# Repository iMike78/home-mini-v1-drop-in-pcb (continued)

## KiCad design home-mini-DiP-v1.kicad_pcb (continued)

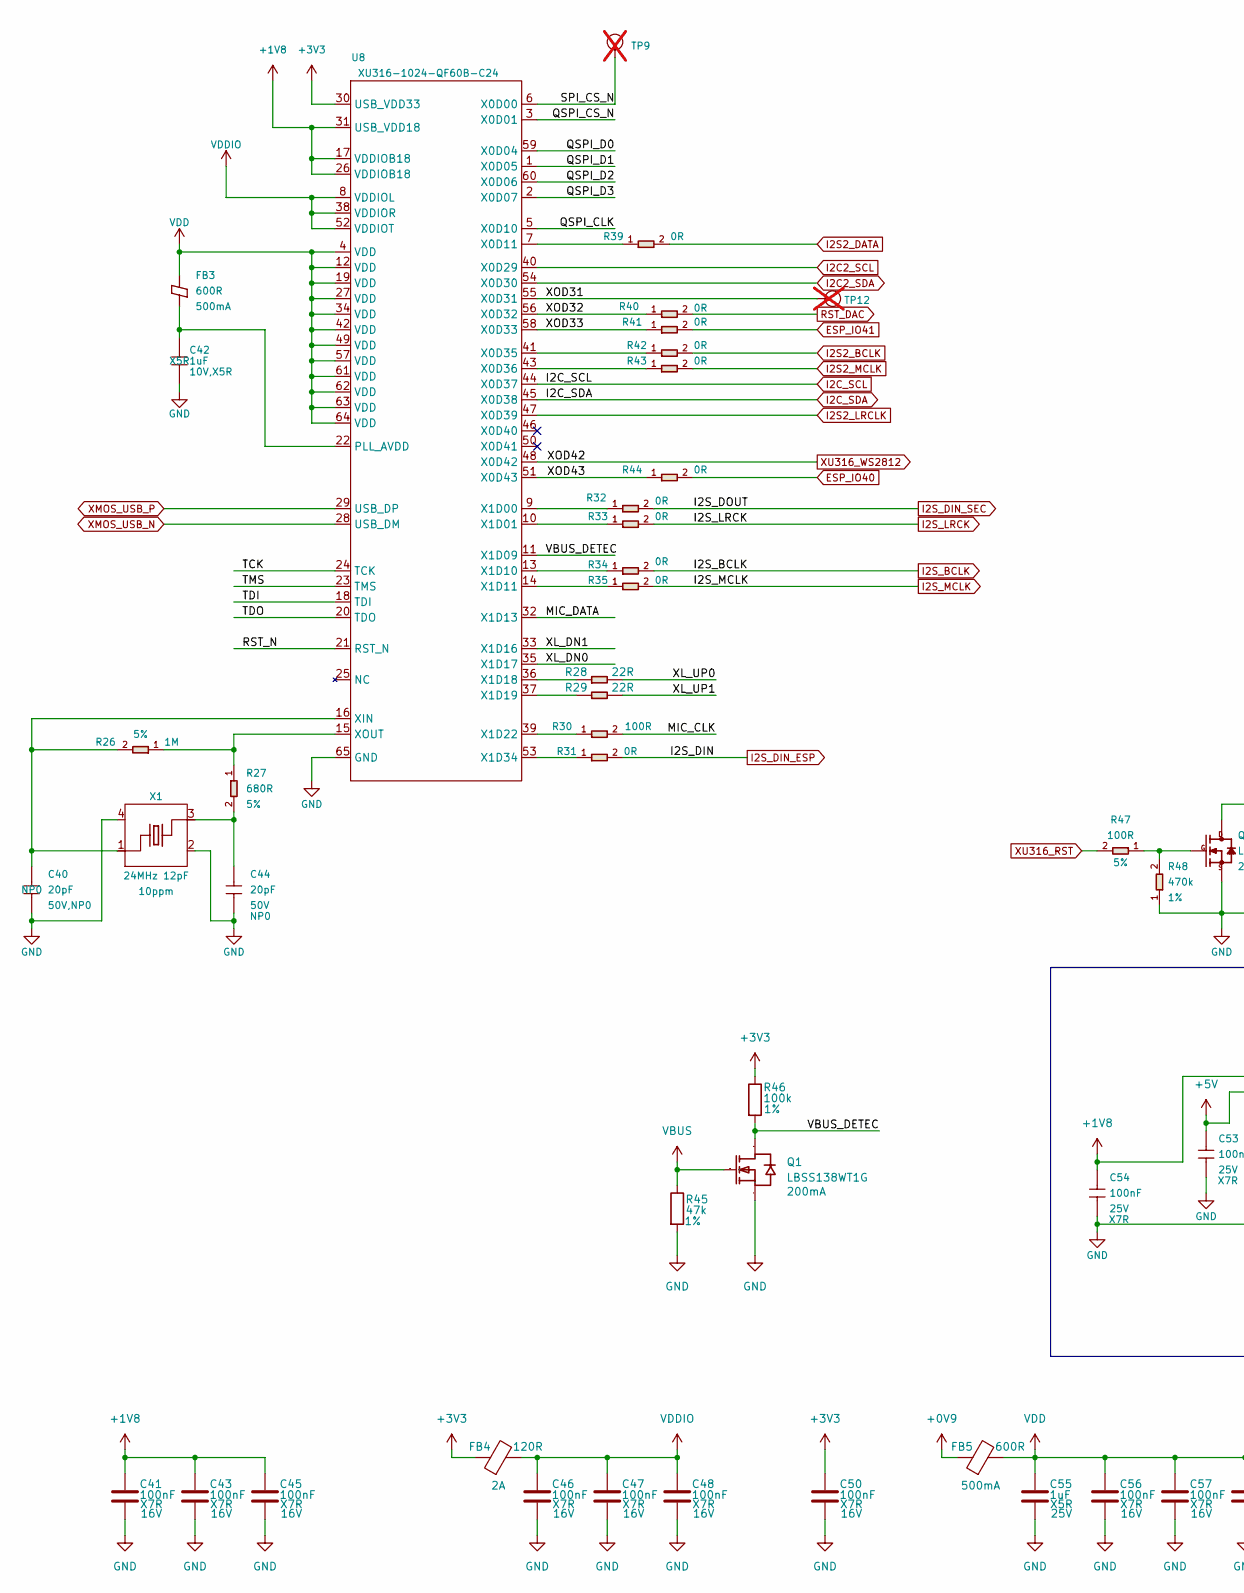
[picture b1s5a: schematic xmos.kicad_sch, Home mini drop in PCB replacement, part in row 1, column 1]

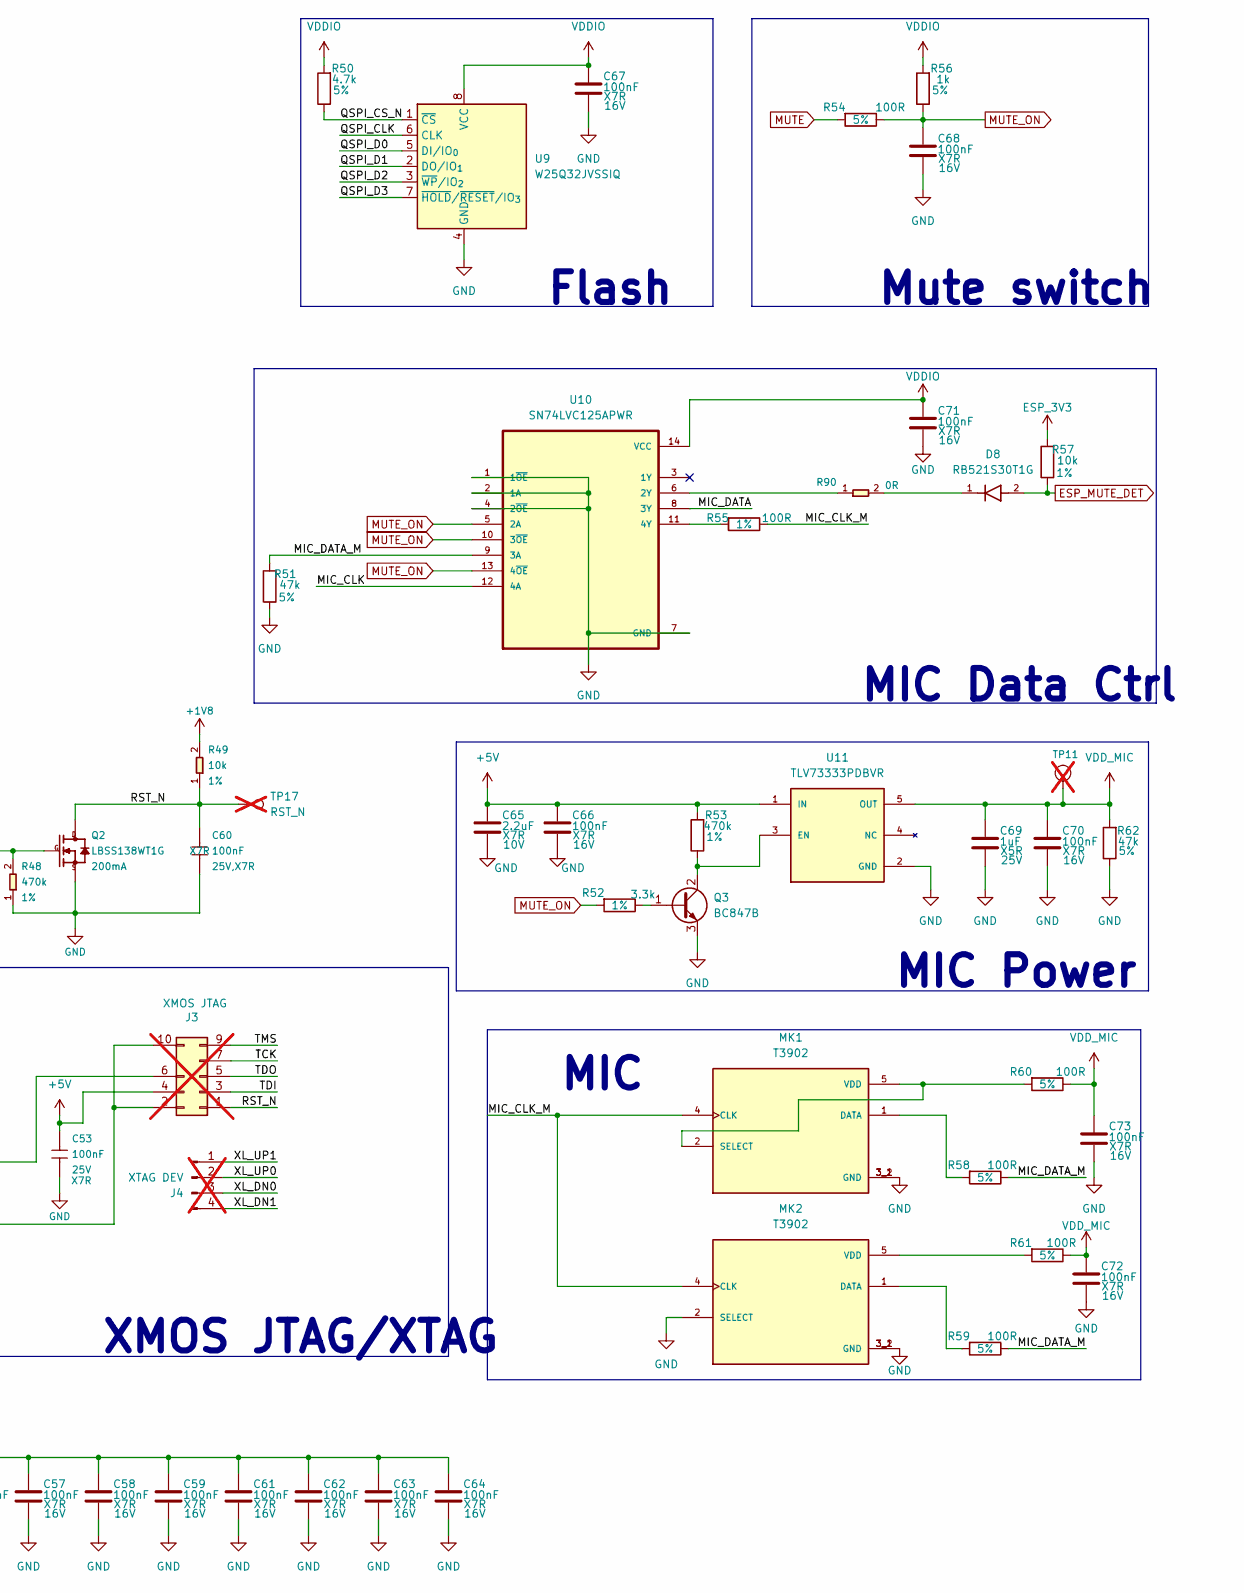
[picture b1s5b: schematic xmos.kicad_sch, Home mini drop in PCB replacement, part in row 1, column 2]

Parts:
C40: 20pF; C_0402_1005Metric; Voltage Rating 50V,NP0; Voltage 50V; MPN 0402CG200J500NT; LCSC Part # C1554
C41, C43, C45, C46, C47, C48, C50, C56, C57, C58, C59, C61, C62, C63, C64, C66, C67, C68, C70, C71, C72, C73: 100nF; C_0402_1005Metric; Voltage 16V; Manufacturer Part CL05B104KO5NNNC; LCSC Part # C1525
C42: 1uF; C_0402_1005Metric; Voltage Rating 10V,X5R; Voltage 25V; MPN CL05A105KA5NQNC; LCSC Part # C52923
C44: 20pF; C_0402_1005Metric; Voltage Rating 50V; Voltage 50V; MPN 0402CG200J500NT; LCSC Part # C1554
C53, C54: 100nF; C_0402_1005Metric; Voltage Rating 25V; Voltage 16V; MPN CL05B104KO5NNNC; LCSC Part # C1525
C55, C69: 1uF; C_0402_1005Metric; Voltage 25V; Manufacturer Part CL05A105KA5NQNC; LCSC Part # C52923
C60: 100nF; C_0402_1005Metric; Voltage Rating 25V,X7R; MPN CL05B104KO5NNNC; LCSC Part # C1525
C65: 2.2uF; C_0603_1608Metric; Voltage 10V; Manufacturer Part GRM188R71A225KE15D; LCSC Part # C86018
D8: RB521S30T1G; DIOM168X70N; Manufacturer Part RB521S30T1G; LCSC Part # C27636108
FB3: 600R; BLM18PG121SN1D; Rating 500mA; MPN BLM18KG601SN1D; LCSC Part # C85833
FB4: 120R; BLM18PG121SN1D; Manufacturer Part BLM18PG121SN1D; LCSC Part # C14709
FB5: 600R; BLM18PG121SN1D; Manufacturer Part BLM18KG601SN1D; LCSC Part # C85833
J3: XMOS JTAG; PinHeader_2x05_P2.54mm_Vertical; not fitted
J4: XTAG DEV; PinHeader_1x04_P2.54mm_Vertical; not fitted
MK1, MK2: T3902; MIC_T3902; Manufacturer Part MMICT390200012; LCSC Part # C3171752
Q1: LBSS138WT1G; SOT-323_SC-70; Manufacturer Part LBSS138WT1G; LCSC Part # C383201
Q2: LBSS138WT1G; SOT-323_SC-70; Rating 200mA; MPN LBSS138WT1G; LCSC Part # C383201
Q3: BC847B; SOT-23; Manufacturer Part BC847B; LCSC Part # C20069135
R26: 1M; R_0402_1005Metric; Power Rating 5%; MPN 0402WGF1004TCE; LCSC Part # C26083
R27: 680R; R_0402_1005Metric; Power Rating 5%; MPN 0402WGF6800TCE; LCSC Part # C25130
R28, R29: 22R; R_0402_1005Metric; Power Rating 5%; MPN 0402WGF220JTCE; LCSC Part # C25092
R30, R47: 100R; R_0402_1005Metric; Power Rating 5%; MPN 0402WGF1000TCE; LCSC Part # C25076
R31, R32, R33, R34, R35, R41, R42, R43, R44: 0R; R_0402_1005Metric; Power Rating 5%; MPN 0402WGF0000TCE; LCSC Part # C17168
R39, R40, R90: 0R; R_0402_1005Metric; Tolerance 5%; MPN 0402WGF0000TCE; LCSC Part # C17168
R45: 47k; R_0402_1005Metric; Tolerance 1%; Manufacturer Part 0402WGF4702TCE; LCSC Part # C25792
R46: 100k; R_0402_1005Metric; Tolerance 1%; Manufacturer Part 0402WGJ0104TCE; LCSC Part # C25530
R48: 470k; R_0402_1005Metric; Power Rating 1%; MPN 0402WGF4703TCE; LCSC Part # C25790
R49: 10k; R_0402_1005Metric; Power Rating 1%; MPN 0402WGF1002TCE; LCSC Part # C25744
R50: 4.7k; R_0402_1005Metric; Tolerance 5%; Manufacturer Part 0402WGF4701TCE; LCSC Part # C25900
R51, R62: 47k; R_0402_1005Metric; Tolerance 5%; Manufacturer Part 0402WGF4702TCE; LCSC Part # C25792
R52: 3.3k; R_0402_1005Metric; Tolerance 1%; Manufacturer Part 0402WGF3301TCE; LCSC Part # C25890
R53: 470k; R_0402_1005Metric; Tolerance 1%; Manufacturer Part 0402WGF4703TCE; LCSC Part # C25790
R54: 100R; R_0402_1005Metric; Tolerance 5%; Power Rating 5%; Manufacturer Part 0402WGF1000TCE; LCSC Part # C25076
R55: 100R; R_0402_1005Metric; Tolerance 1%; Manufacturer Part 0402WGF1000TCE; LCSC Part # C25076
R56: 1k; R_0402_1005Metric; Tolerance 5%; Manufacturer Part 0402WGF1001TCE; LCSC Part # C11702
R57: 10k; R_0402_1005Metric; Tolerance 1%; Manufacturer Part 0402WGF1002TCE; LCSC Part # C25744
R58, R59, R60, R61: 100R; R_0402_1005Metric; Tolerance 5%; Manufacturer Part 0402WGF1000TCE; LCSC Part # C25076
TP9, TP11: TEST-POINT; TestPoint_Pad_D1.0mm; not fitted
TP12: Test Point; TestPoint_Pad_D1.0mm; Part Type Test Point; not fitted
TP17: RST_N; TestPoint_Pad_D1.0mm; not fitted
U8: XU316-1024-QF60B-C24​; XU316-1024-QF60B-C24; MPN XU316-1024-QF60B-C24; LCSC Part # C6617472
U9: W25Q32JVSSIQ; SOIC-8_5.3x5.3mm_P1.27mm; Manufacturer Part W25Q32JVSSIQ; LCSC Part # C179173
U10: SN74LVC125APWR; SOP65P640X120-14N; Manufacturer Part SN74LVC125APWR; LCSC Part # C7813
U11: TLV73333PDBVR; Manufacturer Part TLV73333PDBVR; LCSC Part # C134139
X1: 24MHz 12pF; X4-SMD-2.0X1.6MM; Rating 10ppm; MPN 7F24000E12UCG; LCSC Part # C252273

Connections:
+0V9: FB5.1; also elsewhere on the board
+1V8: C41.1, C43.1, C45.1, C54.1, J3.6, R49.2, U8.17 (VDDIOB18), U8.26 (VDDIOB18), U8.31 (USB_VDD18); also elsewhere on the board
+3V3: C50.1, FB4.1, R46.1, U8.30 (USB_VDD33); also elsewhere on the board
+5V: C53.1, C65.1, C66.1, J3.4, R53.2, U11.1 (IN); also elsewhere on the board
/XMOS/MIC_CLK: R30.2, U10.12 (4A)
/XMOS/MIC_CLK_M: MK1.4 (CLK), MK2.4 (CLK), R55.1
/XMOS/MIC_DATA: U8.32 (X1D13), U10.8 (3Y)
/XMOS/MIC_DATA_M: R51.2, R58.1, R59.1, U10.9 (3A)
/XMOS/QSPI_CLK: U8.5 (X0D10), U9.6 (CLK)
/XMOS/QSPI_CS_N: R50.1, U8.3 (X0D01), U9.1 (~CS)
/XMOS/QSPI_D0: U8.59 (X0D04), U9.5 (DI/IO_{0})
/XMOS/QSPI_D1: U8.1 (X0D05), U9.2 (DO/IO_{1})
/XMOS/QSPI_D2: U8.60 (X0D06), U9.3 (~WP/IO_{2})
/XMOS/QSPI_D3: U8.2 (X0D07), U9.7 (~HOLD/~RESET/IO_{3})
/XMOS/RST_N: C60.1, J3.1, Q2.3 (D), R49.1, TP17.1, U8.21 (RST_N)
/XMOS/SPI_CS_N: TP9.1 (T), U8.6 (X0D00)
/XMOS/TCK: J3.7, U8.24 (TCK)
/XMOS/TDI: J3.3, U8.18 (TDI)
/XMOS/TDO: J3.5, U8.20 (TDO)
/XMOS/TMS: J3.9, U8.23 (TMS)
/XMOS/VBUS_DETEC: Q1.3 (D), R46.2, U8.11 (X1D09)
/XMOS/XL_DN0: J4.3, U8.35 (X1D17)
/XMOS/XL_DN1: J4.4, U8.33 (X1D16)
/XMOS/XL_UP0: J4.2, R28.2
/XMOS/XL_UP1: J4.1, R29.2
/XMOS/XOD31: TP12.1 (T), U8.55 (X0D31)
/XMOS/XOD32: R40.1, U8.56 (X0D32)
/XMOS/XOD33: R41.1, U8.58 (X0D33)
/XMOS/XOD43: R44.1, U8.51 (X0D43)
ESP_3V3: R57.2; also elsewhere on the board
ESP_IO40: R44.2; also elsewhere on the board
ESP_IO41: R41.2; also elsewhere on the board
ESP_MUTE_DET: D8.2, R57.1; also elsewhere on the board
GND: C40.2, C41.2, C42.2, C43.2, C44.2, C45.2, C46.2, C47.2, C48.2, C50.2, C53.2, C54.2, C55.2, C56.2, C57.2, C58.2, C59.2, C60.2, C61.2, C62.2, C63.2, C64.2, C65.2, C66.2, C67.2, C68.2, C69.2, C70.2, C71.2, C72.2, C73.2, J3.2, J3.10, MK1.3_1 (GND), MK1.3_2 (GND), MK2.2 (SELECT), MK2.3_1 (GND), MK2.3_2 (GND), Q1.2 (S), Q2.2 (S), Q3.3 (E), R45.2, R48.1, R51.1, R62.1, U8.65 (GND), U9.4 (GND), U10.1 (1~OE), U10.2 (1A), U10.4 (2~OE), U10.7 (GND), U11.2 (GND), X1.2, X1.4; also elsewhere on the board
I2C2_SCL: U8.40 (X0D29); also elsewhere on the board
I2C2_SDA: U8.54 (X0D30); also elsewhere on the board
I2C_SCL: U8.44 (X0D37); also elsewhere on the board
I2C_SDA: U8.45 (X0D38); also elsewhere on the board
I2S2_BCLK: R42.2; also elsewhere on the board
I2S2_DATA: R39.2; also elsewhere on the board
I2S2_LRCLK: U8.47 (X0D39); also elsewhere on the board
I2S2_MCLK: R43.2; also elsewhere on the board
I2S_BCLK: R34.2; also elsewhere on the board
I2S_DIN_ESP: R31.2; also elsewhere on the board
I2S_DIN_SEC: R32.2; also elsewhere on the board
I2S_LRCK: R33.2; also elsewhere on the board
I2S_MCLK: R35.2; also elsewhere on the board
MUTE: R54.2; also elsewhere on the board
MUTE_ON: C68.1, R52.2, R54.1, R56.1, U10.5 (2A), U10.10 (3~OE), U10.13 (4~OE)
unnamed: C44.1, R27.2, X1.3
unnamed: D8.1, R90.2
unnamed: MK1.1 (DATA), R58.2
unnamed: MK1.2 (SELECT), MK1.5 (VDD), R60.2
unnamed: MK2.1 (DATA), R59.2
unnamed: MK2.5 (VDD), R61.2
unnamed: Q2.1 (G), R47.1, R48.2
unnamed: Q3.1 (B), R52.1
unnamed: Q3.2 (C), R53.1, U11.3 (EN)
unnamed: C42.1, FB3.1, U8.22 (PLL_AVDD)
unnamed: R39.1, U8.7 (X0D11)
unnamed: R42.1, U8.41 (X0D35)
unnamed: R43.1, U8.43 (X0D36)
unnamed: R32.1, U8.9 (X1D00)
unnamed: R33.1, U8.10 (X1D01)
unnamed: R34.1, U8.13 (X1D10)
unnamed: R35.1, U8.14 (X1D11)
unnamed: R28.1, U8.36 (X1D18)
unnamed: R29.1, U8.37 (X1D19)
unnamed: R30.1, U8.39 (X1D22)
unnamed: R31.1, U8.53 (X1D34)
unnamed: C40.1, R26.2, U8.16 (XIN), X1.1
unnamed: R26.1, R27.1, U8.15 (XOUT)
unnamed: R90.1, U10.6 (2Y)
unnamed: R55.2, U10.11 (4Y)
RST_DAC: R40.2; also elsewhere on the board
VBUS: Q1.1 (G), R45.1; also elsewhere on the board
VDD: C55.1, C56.1, C57.1, C58.1, C59.1, C61.1, C62.1, C63.1, C64.1, FB3.2, FB5.2, U8.4 (VDD), U8.12 (VDD), U8.19 (VDD), U8.27 (VDD), U8.34 (VDD), U8.42 (VDD), U8.49 (VDD), U8.57 (VDD), U8.61 (VDD), U8.62 (VDD), U8.63 (VDD), U8.64 (VDD)
VDDIO: C46.1, C47.1, C48.1, C67.1, C71.1, FB4.2, R50.2, R56.2, U8.8 (VDDIOL), U8.38 (VDDIOR), U8.52 (VDDIOT), U9.8 (VCC), U10.14 (VCC)
VDD_MIC: C69.1, C70.1, C72.1, C73.1, R60.1, R61.1, R62.2, TP11.1 (T), U11.5 (OUT)
XMOS_USB_N: U8.28 (USB_DM)
XMOS_USB_P: U8.29 (USB_DP)
XU316_RST: R47.2; also elsewhere on the board
XU316_WS2812: U8.48 (X0D42)

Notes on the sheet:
Flash
MIC
Mute switch
MIC Power
MIC Data Ctrl
XMOS JTAG/XTAG

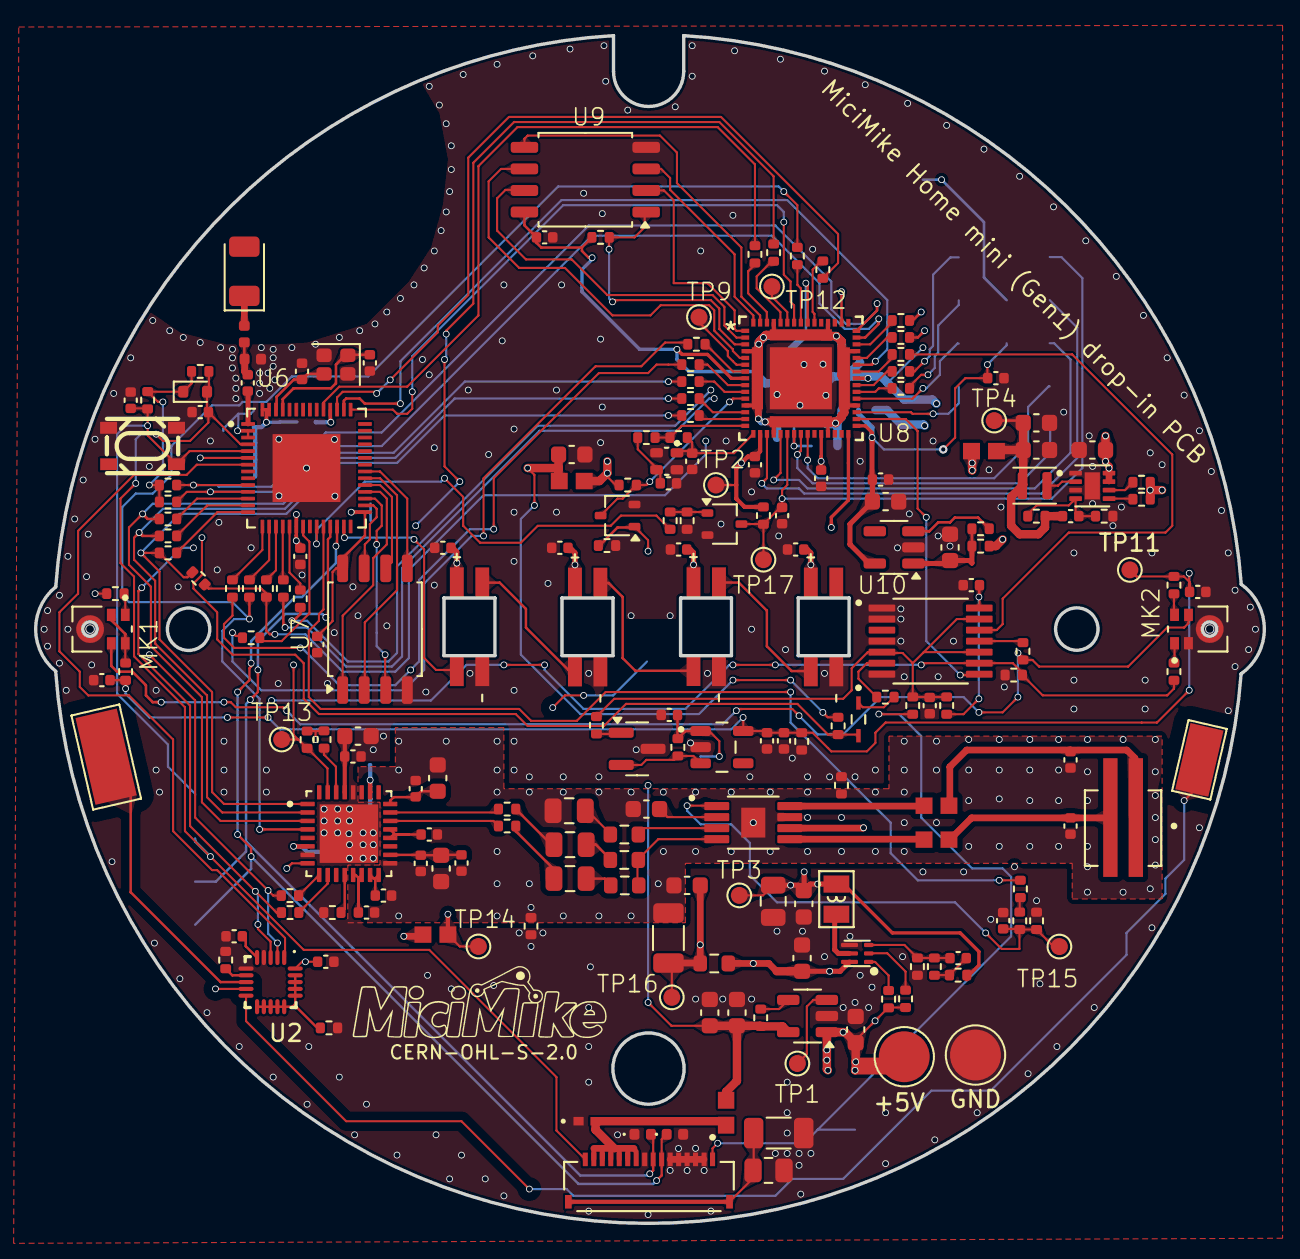
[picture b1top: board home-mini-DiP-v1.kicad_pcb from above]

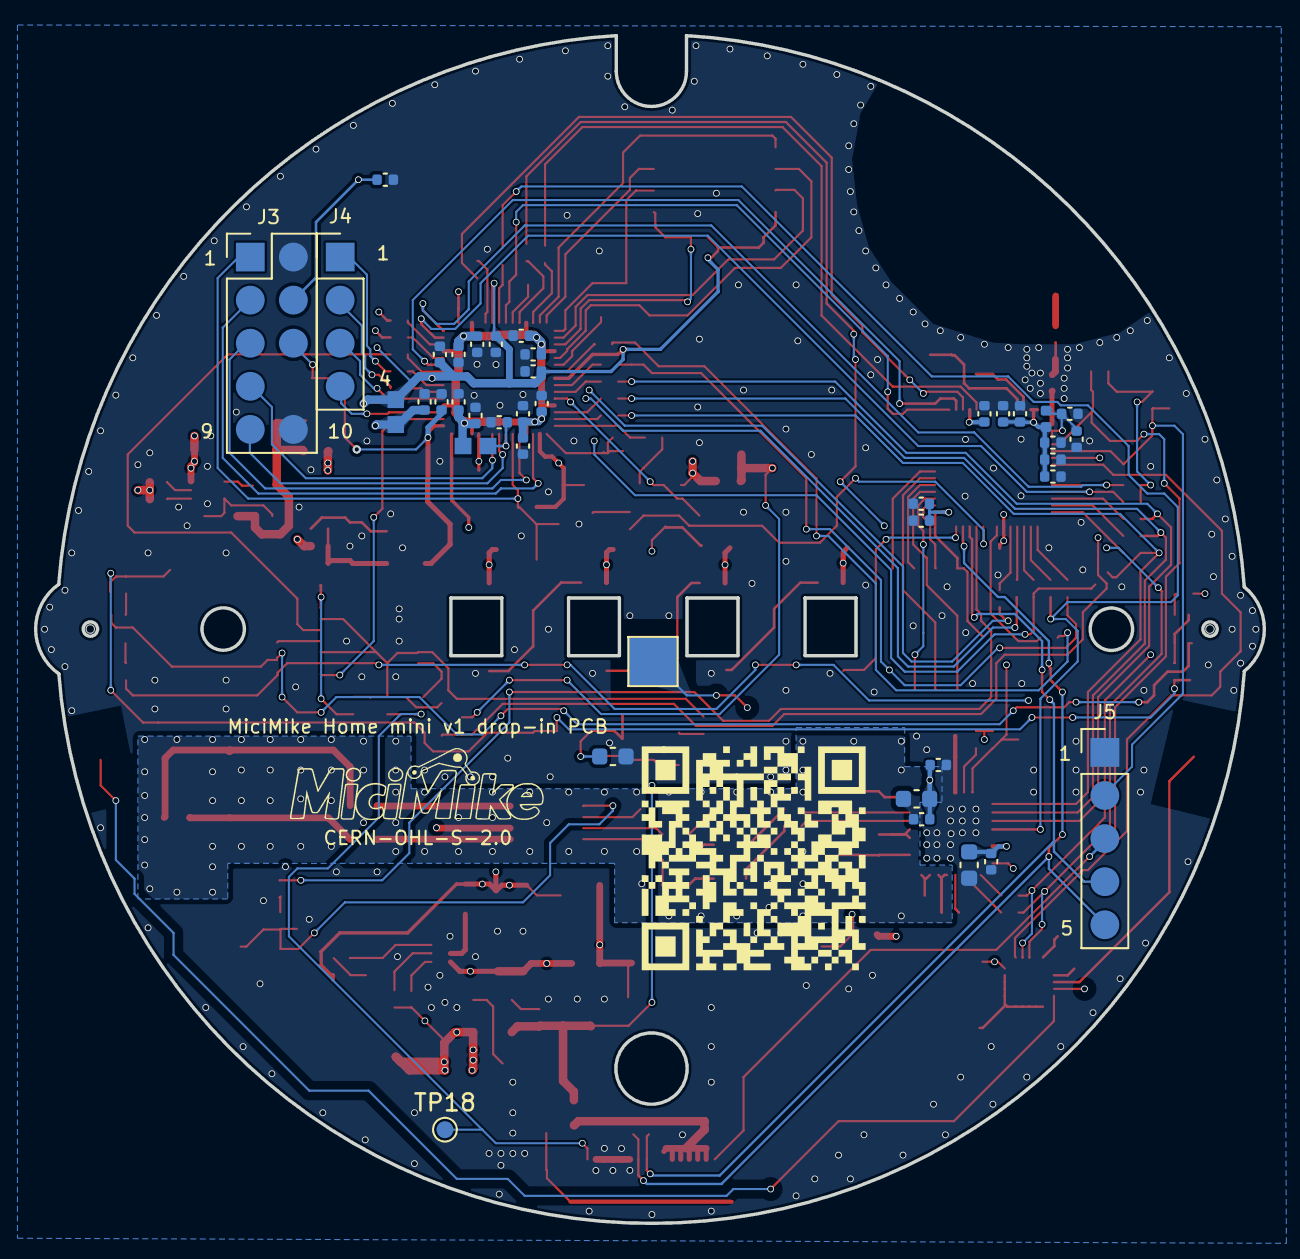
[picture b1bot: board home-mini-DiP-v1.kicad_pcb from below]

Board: 4 copper layers, 72.4 x 70.0 mm, 241 parts (40 on the bottom side), 161 nets.

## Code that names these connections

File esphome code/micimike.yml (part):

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
i2c:
  - id: internal_i2c
    sda: GPIO5
    scl: GPIO6
    frequency: 400kHz

psram:
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      - delay: 15min
      - switch.turn_off: timer_ringing
  - platform: gpio
    pin: GPIO18
    id: internal_speaker_amp
    name: "Internal speaker amp"
    entity_category: config
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    id: hardware_mute_switch
    internal: true
    pin: 
      number: GPIO1
      mode: input_pullup
      inverted: false
    on_press:
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
  - platform: esp32_touch
    id: volume_up
    pin: GPIO2
    threshold: 10000
    on_press:
      - if:
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light:
  - platform: esp32_rmt_led_strip
    id: leds_internal
    pin: GPIO21
    chipset: SK6812
    max_refresh_rate: 15ms
    num_leds: 4
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
i2s_audio:
  - id: i2s_output
    # i2s_output data pin is gpio10
    i2s_lrclk_pin:
      number: GPIO7
    i2s_bclk_pin:
      number: GPIO8

  - id: i2s_input
    # data line is GPIO15
    i2s_lrclk_pin:
      number: GPIO14
    i2s_bclk_pin:
      number: GPIO13

microphone:
  - platform: i2s_audio
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    id: i2s_audio_speaker
    sample_rate: 48000
    i2s_mode: secondary
    i2s_dout_pin: GPIO10
    bits_per_sample: 32bit
    i2s_audio_id: i2s_output
    dac_type: external
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
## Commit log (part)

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2025-08-05 routing
2025-08-05 work in progress
2025-08-07 Update README.md paraphrase copy from MiciMike Nest Mini project
    Update README.md with paraphrase copy from MiciMike Nest Mini project
2025-08-07 Correct link to new repo
    Correct link to new repo
2025-08-08 getting ready for production
2025-08-10 update for production
2025-09-16 error corrections
2025-10-02 prepare for the 1st test batch
2025-10-25 routing done
2025-11-04 ready for the 1st test batch
2025-11-29 mods after 1st batch testing
2025-12-01 Add a picture of first the batch prototype to README
    Add a picture of first the batch prototype to README
2025-12-01 Add picture of first the batch prototype for README
    Add picture of first the batch prototype for README
2025-12-03 final mods before production
2025-12-04 example working esphome code based on HA VPE
2025-12-04 Update project status and hardware specifications
2025-12-04 Revise project status and update hardware details
    Updated the README to reflect changes in project status and hardware specifications.
2025-12-07 Update README with PCB ordering and discussion links
    Added ordering information and a discussion link for the PCB.
2025-12-07 Update README with extra component requirement
    Added information about an extra component required for PCB installation.
2025-12-07 Add step-by-step guide link to README
2025-12-08 Update FPC cable description in README
2025-12-08 Revise PCB order procedure reference in README
    Updated the link for PCB order procedure information.
2025-12-12 Add note about potential Crowd Supply campaign
    Added a note regarding the evaluation of a Crowd Supply campaign for the project.
2025-12-31 Request for ESPHome contributors and collaboration
    Added a section seeking ESPHome contributors for project collaboration and testing.
2026-01-02 Update README with PCB details and image
    Added an image to the README and clarified PCB details.
2026-02-15 esphome code bugfix
    volume_down loop fixed
2026-02-28 Silkscreen clearout
2026-02-28 version number bug update
2026-03-17 Update README fixing image link and mention crowdfunding
    Update README to both fix the image link and also added mentioning of the upcoming crowdfunding campaign and its related project link.
2026-03-17 Revise crowdfunding campaign details in README
    Updated the crowdfunding campaign information in README.
2026-04-07 esphome 2026.3 update
2026-04-07 pcb antenna finetuning
2026-04-28 Update crowdfunding campaign status in README
    Updated the crowdfunding campaign status in the README.
2026-04-28 Enhance crowdfunding update with subscription details
    Expanded the update section to include subscription information for email updates.
2026-04-28 Clarify crowdfunding campaign update in README
    Reworded the update about the crowdfunding campaign for clarity.
2026-05-02 repository cleanup
2026-05-10 v2 hardware revision
    MPR121 touch controller added to replace esp32-s3 integrated touch pins
2026-05-10 not relevant to this repo
2026-05-10 Update README for v0.9.5 changes and test points
    Updated README to include v0.9.5 changes regarding the touch controller migration to MPR121 and added new solderable test points.
2026-05-16 v2 hardware
2026-05-22 Update README remove changelog moving to seperate file
    Removed changelog section to move that information to its own changelog.md file instead
2026-05-22 Add changelog file for the project
    Added a changelog.md file for MiciMike drop-in PCB replacement for Google Home Mini (Gen-1) project, moving information previously posted in the README.md file, with first commit detailing updates in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
2026-06-12 production update + esphome fw update + latest render pics
2026-06-12 Alexa removed as a wakeword option
2026-06-12 version update
